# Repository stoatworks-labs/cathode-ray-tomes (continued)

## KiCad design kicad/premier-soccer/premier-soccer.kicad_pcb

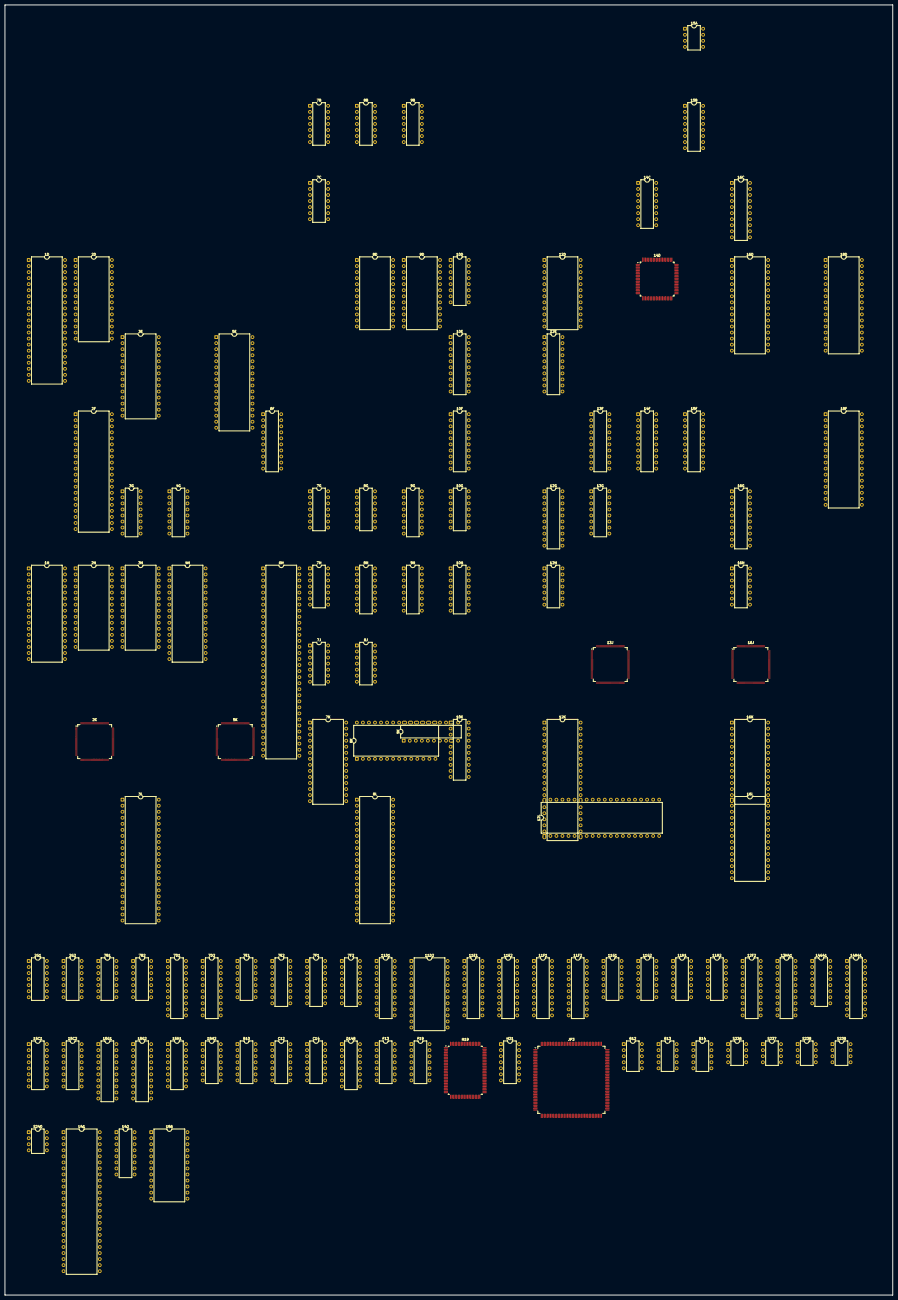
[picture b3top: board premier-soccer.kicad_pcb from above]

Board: 2 copper layers, 373.1 x 542.2 mm, 114 parts (0 on the bottom side), 699 nets, no tracks yet.

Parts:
1D, 3L, 8L: HN624116P; DIP-42_W15.24mm
1H, 4H, 5E: M27C4001; DIP-32_W15.24mm
2D: SRAM32K8B; DIP-28_W15.24mm
2F: Z80CPU; DIP-40_W15.24mm
2G1: 74LS00; DIP-14_W7.62mm
2G2, 7J, 8G: 74LS08; DIP-14_W7.62mm
2H, 3H, 7K, 8K: SRAM64K10; DIP-28_W15.24mm
2K: 053244-A; TQFP-120_14x14mm_P0.4mm
3E: SRAM8K8B; DIP-28_W15.24mm
3G: 74LS139; DIP-16_W7.62mm
4G: 74F138; DIP-16_W7.62mm
5K: 053245-A; TQFP-120_14x14mm_P0.4mm
6F: PAL16L8; DIP-20_W7.62mm
6H: MC68000; DIP-64_W15.24mm
7B, 7B1, 7B2, 8B, 9B: 74LS07; DIP-14_W7.62mm
7C, 7E1, 11H2, 12H, 15H2: 74LS32; DIP-14_W7.62mm
7D1, 7D2, 12G, 16C: 74LS273; DIP-20_W7.62mm
7E2: 74LS138; DIP-16_W7.62mm
7F1, 8H, 9H, 10H, 13G: 74LS157; DIP-16_W7.62mm
7F2, 15C2: 74LS174; DIP-16_W7.62mm
7G, 11H1, 16H: 74LS74; DIP-14_W7.62mm
7H: 74F74; DIP-14_W7.62mm
8D, 9D: HM6116P-3; DIP-24_W15.24mm
8J: 74LS10; DIP-14_W7.62mm
9G: 74LS175; DIP-16_W7.62mm
9K, 10E, 10F, 10K, 11E1, 11F1, 11F2, 12F2, 13H41, 14H41, 16G: 74LS245; DIP-20_W7.62mm
10D, 14G41, 15H1: 74LS367; DIP-16_W7.62mm
10G, 11G1, 11G2: 74LS04; DIP-14_W7.62mm
11D1, 11E2, 12E, 15G1, 15G2: 74LS244; DIP-20_W7.62mm
11D2, 12D: SRAM16KSL45; DIP-24_W15.24mm
12K, 12L: 955D05-06-07-08; DIP-40_W15.24mm
13F, 14F, 15F: 74LS374; DIP-20_W7.62mm
13J: 051962; TQFP-120_14x14mm_P0.4mm
14C, 15B, 15C1: 74LS257; DIP-16_W7.62mm
14D: 053936; PQFP-80_14x14mm_P0.65mm
15A: ER5911; DIP-8_W7.62mm
16D, 18D: 27C1000; DIP-32_W15.24mm
16J: 052109; TQFP-120_14x14mm_P0.4mm
16K, 16L: MB8464A-10W-15W; DIP-28_W15.24mm
18F: DIP-32_W15.24mm
B10: LM324; DIP-14_W7.62mm
C12: 74LS20; DIP-14_W7.62mm
C14: 74LS04; DIP-14_W7.62mm
D14B: 74LS257; DIP-16_W7.62mm
F13: 74LS32; DIP-14_W7.62mm
F19: 74LS74; DIP-14_W7.62mm
H19: 053251; PQFP-100_14x20mm_P0.65mm
H21: 74LS04; DIP-14_W7.62mm
JP3: 054539; PQFP-160_28x28mm_P0.65mm
R12, R13, R14: 052535; DIP-10_W7.62mm
S236, S237, S238, S239, S240: KONAMI_005273; DIP-8_W7.62mm
U41: 054321; DIP-48_W15.24mm
U42: AD1868R; DIP-16_W7.62mm
U56: 051550; DIP-24_W15.24mm

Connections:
/1.54CLK: JP3.28, U41.7, U42.4
/3GA_P5: 2G1.1, 3G.5, U56.1
/3GP4: 3G.4, 7E1.1, 7E1.4, 7G.12
/7E2P13: 7E1.9, 7E1.12, 7E2.13
/11G1P8: 7G.3, 9G.9, 11G1.8, 11H1.11, 16H.11
/11H1P9: 7C.5, 10D.1, 11D1.1, 11D1.19, 11H1.9, 12H.12
/COIN_CNT_1: U56.22, U56.23
/COIN_CNT_2: U56.20, U56.21
/CPU~EN: 5K.26, 11G2.13, 15C1.14, 15H2.5
/DFI0: 13J.59, H19.47
/DFI1: 13J.60, H19.48
/DFI2: 13J.62, H19.49
/DFI3: 13J.63, H19.50
/DFI5: 13J.65, H19.51
/DFI6: 13J.66, H19.52
/DFI7: 13J.67, H19.54
/DO: 15A.4, 15C1.3
/DSA0: 13J.46, H19.57
/DSA1: 13J.47, H19.58
/DSA2: 13J.48, H19.59
/DSA3: 13J.49, H19.60
/DSA5: 13J.51, H19.61
/DSA6: 13J.52, H19.62
/DSA7: 13J.53, H19.63
/DSB0: 13J.30, H19.66
/DSB1: 13J.32, H19.67
/DSB2: 13J.33, H19.68
/DSB3: 13J.34, H19.69
/DSB5: 13J.36, H19.70
/DSB6: 13J.37, H19.71
/DSB7: 13J.38, H19.72
/IOCS: 7E2.15, 14C.15, 15B.15, 15C1.15, D14B.15
/M6: 2K.10, 5K.10, 7D1.11, 7D2.11, 11H1.3, 12G.11, 13F.11, 13J.78, 14D.64, 14F.11, 15F.11, 16H.3, H19.41
/M12: 2K.12, 5K.12, 13J.95
/MAINR~W: 7C.2, 7C.4, 7C.8, 7C.13, U41.31
/MAIN_A1: 1H.12, 2H.10, 3H.10, 4H.12, 6H.29, 7J.5, 8H.2, 11D1.2, 11E2.2, 13J.89, 15G1.2, 15H1.2
/MAIN_A2: 1H.11, 2H.9, 3H.9, 4H.11, 5K.25, 6H.30, 8H.5, 11D1.4, 11E2.4, 15G1.4, 15H1.4
/MAIN_A3: 1H.10, 2H.8, 3H.8, 4H.10, 5K.24, 6H.31, 8H.11, 11D1.6, 11E2.6, 15G1.6, 15H1.6
/MAIN_A4: 1H.9, 2H.7, 3H.7, 4H.9, 5K.23, 6H.32, 8H.14, 11D1.8, 11E2.8, 15G1.8, 15H1.10
/MAIN_A5: 1H.8, 2H.6, 3H.6, 4H.8, 6H.33, 7J.1, 10H.2, 11D1.11, 11E2.11, 15G1.11, 15H1.12
/MAIN_A6: 1H.7, 2H.5, 3H.5, 4H.7, 6H.34, 7J.13, 10H.5, 11D1.13, 11E2.13, 15G1.13, 15H1.14
/MAIN_A7: 1H.6, 2H.4, 3H.4, 4H.6, 5K.22, 6H.35, 10H.11, 11D1.15, 11E2.15, 15G1.15, 16J.114
/MAIN_A8: 1H.5, 2H.3, 3H.3, 4H.5, 5K.20, 6H.36, 10H.14, 11D1.17, 11E2.17, 15G1.17, 16J.113
/MAIN_A9: 1H.27, 2H.25, 3H.25, 4H.27, 5K.19, 6H.37, 9H.2, 10D.2, 12E.2, 15G2.2, 16J.112
/MAIN_A10: 1H.26, 2H.24, 3H.24, 4H.26, 5K.18, 6H.38, 9H.5, 10D.4, 12E.4, 15G2.4, 16J.111
/MAIN_A11: 1H.23, 2H.21, 3H.21, 4H.23, 5K.17, 6H.39, 9H.11, 10D.6, 12E.6, 15G2.6, 16J.110
/MAIN_A12: 1H.25, 2H.23, 3H.23, 4H.25, 5K.15, 6H.40, 7E2.1, 12E.8, 15G2.8
/MAIN_A13: 1H.4, 2H.2, 3H.2, 4H.4, 5K.14, 6H.41, 7E2.2, 12E.11, 15G2.11, 16J.109
/MAIN_A14: 1H.28, 4G.1, 4H.28, 6H.42, 7E2.3, 12E.13, 15G2.13, 16J.80
/MAIN_A15: 1H.29, 4G.2, 4H.29, 6H.43, 12E.15, 15G2.15, 16J.82
/MAIN_A16: 1H.3, 4G.3, 4H.3, 6H.44, 12E.17, 15G2.17, 16J.83
/MAIN_A17: 1H.2, 4G.5, 4H.2, 6H.45, 7E2.6, 10D.12, 14G41.2
/MAIN_A18: 1H.30, 4H.30, 6H.46, 14G41.4
/MAIN_A19: 6H.47, 14G41.6
/MAIN_ABUF0: 2K.19, 15H1.3, 16J.66, H19.85
/MAIN_ABUF1: 2K.18, 15H1.5, 16J.67, H19.84
/MAIN_ABUF2: 2K.17, 15H1.7, 16J.68, H19.83
/MAIN_ABUF3: 2K.15, 15H1.9, 16J.69, H19.82
/MAIN_ABUF4: 15H1.11, 16J.116
/MAIN_ABUF5: 15H1.13, 16J.115
/MAIN_D0: 2K.29, 3H.11, 4H.13, 6H.5, 9K.2, 10F.2, 11F1.2, 14H41.2, 16C.3, 16G.2, D14B.4, H19.80, U41.44
/MAIN_D1: 2K.28, 3H.12, 4H.14, 6H.4, 9K.3, 10F.3, 11F1.3, 14H41.3, 16C.4, 16G.3, D14B.7, H19.79, U41.43
/MAIN_D2: 2K.27, 3H.13, 4H.15, 6H.3, 9K.4, 10F.4, 11F1.4, 14H41.4, 16C.7, 16G.4, D14B.9, H19.77, U41.42
/MAIN_D3: 2K.26, 3H.15, 4H.17, 6H.2, 7E2.14, 9K.5, 10F.5, 11F1.5, 14H41.5, 16C.8, 16G.5, D14B.12, H19.76, U41.41
/MAIN_D4: 2K.25, 3H.16, 4H.18, 6H.1, 9K.6, 10F.6, 11F1.6, 14H41.6, 15B.4, 16C.13, 16G.6, H19.75, U41.40
/MAIN_D5: 2K.24, 3H.17, 4H.19, 6H.64, 9K.7, 10F.7, 11F1.7, 14H41.7, 15B.7, 16C.14, 16G.7, H19.74, U41.39
/MAIN_D6: 2K.23, 3H.18, 4H.20, 6H.63, 9K.8, 10F.8, 11F1.8, 14H41.8, 15B.9, 16C.17, 16G.8, U41.38
/MAIN_D7: 2K.22, 3H.19, 4H.21, 6H.62, 9K.9, 10F.9, 11F1.9, 14H41.9, 15B.12, 16C.18, 16G.9, U41.37
/MAIN_D8: 1H.13, 2H.11, 6H.61, 10K.2, 11F2.2, 12F2.2, 13H41.2, 15C1.4, 15C2.3
/MAIN_D9: 1H.14, 2H.12, 6H.60, 10K.3, 11F2.3, 12F2.3, 13H41.3, 15C1.7, 15C2.4
/MAIN_D10: 1H.15, 2H.13, 6H.59, 10K.4, 11F2.4, 12F2.4, 13H41.4, 15C1.9, 15C2.6
/MAIN_D11: 1H.17, 2H.15, 6H.58, 10K.5, 11F2.5, 12F2.5, 13H41.5, 15C1.12, 15C2.11
/MAIN_D12: 1H.18, 2H.16, 6H.57, 10K.6, 11F2.6, 12F2.6, 13H41.6, 14C.4
/MAIN_D13: 1H.19, 2H.17, 6H.56, 10K.7, 11F2.7, 12F2.7, 13H41.7, 14C.7
/MAIN_D14: 1H.20, 2H.18, 6H.55, 10K.8, 11F2.8, 12F2.8, 13H41.8, 14C.9
/MAIN_D15: 1H.21, 2H.19, 6H.54, 10K.9, 11F2.9, 12F2.9, 13H41.9, 14C.12
/MAIN_DB0: 10E.2, 11E1.2, 13H41.18, 13J.79, 14H41.18, 16J.56
/MAIN_DB1: 10E.3, 11E1.3, 13H41.17, 13J.80, 14H41.17, 16J.57
/MAIN_DB2: 10E.4, 11E1.4, 13H41.16, 13J.81, 14H41.16, 16J.58
/MAIN_DB3: 10E.5, 11E1.5, 13H41.15, 13J.82, 14H41.15, 16J.59
/MAIN_DB4: 10E.6, 11E1.6, 13H41.14, 13J.83, 14H41.14, 16J.60
/MAIN_DB5: 10E.7, 11E1.7, 13H41.13, 13J.84, 14H41.13, 16J.62
/MAIN_DB6: 10E.8, 11E1.8, 13H41.12, 13J.85, 14H41.12, 16J.63
/MAIN_DB7: 10E.9, 11E1.9, 13H41.11, 13J.86, 14H41.11, 16J.64
/MAIN~IRQ: 6H.23, 6H.25, 16J.87
/MBRIT0: 14G41.10, 16C.15
/MBRIT1: 3L.42, 8L.42, 16C.16
/MBRIT2: 11G2.5, 11H2.5, 16C.19
/MCO~WRH: 7C.3, 8D.21
/MCO~WRL: 9D.21, 12H.3
/NDTACK: 11H1.5, 14D.48
/NLOE: 8G.1, 14D.62, 16H.8
/OBJPXL0: 2K.120, H19.30
/OBJPXL1: 2K.119, H19.31
/OBJPXL2: 2K.118, H19.32
/OBJPXL3: 2K.117, H19.33
/OBJPXL4: 2K.116, H19.34
/OBJPXL5: 2K.115, H19.35
/OBJPXL6: 2K.114, H19.36
/OBJPXL7: 2K.113, H19.37
/OBJPXL8: 2K.112, H19.38
/PALETTE~CS: 4G.13, 7C.1, 8H.1, 9H.1, 10E.19, 10H.1, 11E1.19, 12H.1
/PCM0: JP3.34, U41.1
/PCM1: JP3.26, U41.2
/PCM2: JP3.27, U41.3
/PQ: 7G.11, 12H.4, 16J.89
/PR13: 2K.110, H19.25
/PR14: 2K.109, H19.27
/PSACA1: 14C.1, 14D.74, 15B.1, 15C1.1, D14B.1, U41.35
/PSACA2: 14D.72, U41.34
/PSACA3: 14D.71, U41.33
/PSACA4: 14D.70, U41.32
/PSPXL0: 12G.2, H19.4
/PSPXL1: 12G.6, H19.5
/PSPXL2: 12G.12, H19.6
/PSPXL3: 12G.16, H19.7
/PSPXL4: 12G.5, H19.8
/PSPXL5: 12G.9, H19.9
/PSPXL6: 12G.15, H19.10
/RMSCR~RD: 13J.96, 16C.12, 16J.97
/R/~W: 6H.9, 7C.10, 11G1.5, 11H2.2, 12H.9
/SDI0: 2K.108, H19.95
/SDO0: 10G.9, H19.87
/SDON: 7E2.12, U41.30
/SND~CS: 6F.15, U41.20
/SND~IORQ: 2F.20, U41.29
/SND~RD: 2F.21, 3E.22, 6F.2, JP3.67, U41.25
/S~CLK: 2F.6, 7G.5, U41.5
/WD_OUT1: 16C.2, U56.15
/WD_OUT2: 16C.5, U56.16
/ZOE: 10F.19, 11F2.19, 16H.9
/Z_WE1: 7C.6, 11D2.21
/Z_WE2: 12D.21, 12H.11
/colmix/CO1: 8H.3, H19.19
/colmix/CO2: 8H.6, H19.18
/colmix/CO3: 8H.10, H19.17
/colmix/CO4: 8H.13, H19.16
/colmix/CO5: 10H.3, H19.14
/colmix/CO6: 10H.6, H19.13
/colmix/CO7: 10H.10, H19.12
/colmix/CO8: 10H.13, H19.11
/colmix/CO9: 9H.3, H19.93
/colmix/CO10: 9H.6, H19.92
/colmix/CO11: 9H.10, H19.91
/colmix/MCO1: 8D.8, 8H.4, 9D.8
/colmix/MCO2: 8D.7, 8H.7, 9D.7
/colmix/MCO3: 8D.6, 8H.9, 9D.6
/colmix/MCO4: 8D.5, 8H.12, 9D.5
/colmix/MCO5: 8D.4, 9D.4, 10H.4
/colmix/MCO6: 8D.3, 9D.3, 10H.7
/colmix/MCO7: 8D.2, 9D.2, 10H.9
/colmix/MCO8: 8D.1, 9D.1, 10H.12
/colmix/MCO9: 8D.23, 9D.23, 9H.4
/colmix/MCO10: 8D.22, 9D.22, 9H.7
/colmix/MCO11: 8D.19, 9D.19, 9H.9
/colmix/MCO~OE: 8D.20, 9D.20, 9H.12
/colmix/RGB0: 7D1.3, 9D.9, 11E1.18
/colmix/RGB1: 7D1.4, 9D.10, 11E1.17
/colmix/RGB2: 7D1.7, 9D.11, 11E1.16
/colmix/RGB3: 7D1.8, 9D.13, 11E1.15
/colmix/RGB4: 7D1.13, 9D.14, 11E1.14
/colmix/RGB5: 7D1.14, 9D.15, 11E1.13
/colmix/RGB6: 7D1.17, 9D.16, 11E1.12
/colmix/RGB7: 9D.17, 11E1.11
/colmix/RGB8: 7D2.3, 8D.9, 10E.18
/colmix/RGB9: 7D2.4, 8D.10, 10E.17
/colmix/RGB10: 7D2.7, 8D.11, 10E.16
/colmix/RGB11: 7D2.8, 8D.13, 10E.15
/colmix/RGB12: 7D2.13, 8D.14, 10E.14
/colmix/RGB13: 7D2.14, 8D.15, 10E.13
/colmix/RGB14: 7D2.17, 8D.16, 10E.12
/colmix/RGB15: 7D2.18, 8D.17, 10E.11
/colmix/rgb/B0: 7B1.5, 7D1.16
/colmix/rgb/B1: 7B1.9, 7D1.15
/colmix/rgb/B2: 7B1.3, 7D1.12
/colmix/rgb/B3: 7D1.9, 9B.9
/colmix/rgb/B4: 7B1.1, 7D1.6
/colmix/rgb/G0: 7D1.5, 9B.5
/colmix/rgb/G1: 7D1.2, 8B.13
/colmix/rgb/G2: 7D2.19, 9B.3
/colmix/rgb/G3: 7D2.16, 8B.11
/colmix/rgb/G4: 7D2.15, 9B.1
/colmix/rgb/R0: 7D2.12, 8B.5
/colmix/rgb/R1: 7D2.9, 8B.9
/colmix/rgb/R2: 7D2.6, 9B.13
/colmix/rgb/R3: 7D2.5, 8B.3
/colmix/rgb/R4: 7D2.2, 9B.11
/colmix/rgb/~SHADOW: 7B.3, 7B.5, 7B.13, 7D1.19
/io_cabinet/I1P_BTN_1: 15B.2, S237.1
/io_cabinet/I1P_BTN_2: 15B.5, S237.3
/io_cabinet/I1P_BTN_3: 15B.11, S237.5
/io_cabinet/I1P_DOWN: D14B.14, S236.7
/io_cabinet/I1P_LEFT: D14B.2, S236.1
/io_cabinet/I1P_RIGHT: D14B.5, S236.3
/io_cabinet/I1P_START: 15B.14, S240.1
/io_cabinet/I1P_UP: D14B.11, S236.5
/io_cabinet/I2P_BTN_1: 15B.3, S239.1
/io_cabinet/I2P_BTN_2: 15B.6, S239.3
/io_cabinet/I2P_BTN_3: 15B.10, S239.5
/io_cabinet/I2P_DOWN: D14B.13, S238.7
/io_cabinet/I2P_LEFT: D14B.3, S238.1
/io_cabinet/I2P_RIGHT: D14B.6, S238.3
/io_cabinet/I2P_START: 15B.13, S240.3
/io_cabinet/I2P_UP: D14B.10, S238.5
/io_cabinet/ICOIN_1: 15C1.11, S237.7
/io_cabinet/ICOIN_2: 15C1.10, S239.7
/io_cabinet/ISERVICE1: 15C1.2, S240.5
/main/3G P11: 3G.11, 4G.4, 7E2.4
/main/4GP12: 4G.12, 8G.9, 11H1.12
/main/7CP11: 3H.27, 7C.11
/main/7HP6: 7H.2, 7H.6, 11G1.9
/main/9GP11: 8J.1, 9G.11
/main/10GP6: 4G.6, 8J.5, 8J.9, 9G.4, 10G.6, 11H1.10, 16H.10
/main/11H2 P11: 3G.15, 11H2.11
/main/MAIN_A20: 3G.14, 6H.48
/main/MAIN_A21: 3G.2, 3G.13, 6H.50, 8J.13
/main/MAIN_A23: 6H.52, 8J.3, 10G.11, 11H2.12
/main/MAIN~CLK: 6H.15, 7H.5
/main/VSS: 1H.1, 3G.3, 4H.1, 9G.13, 16H.2
/main/~AS: 6H.6, 7E2.5, 10G.5, 11H2.13
/main/~DTACK: 6H.10, 8J.8
/main/~HALT: 6H.17, 7B2.10
/main/~RAM_CS: 4G.15, 7C.12, 15H2.10, 15H2.12
/main/~ROM_CS: 1H.24, 3G.12, 4H.24
/main/~VPA: 6H.21, 8J.6
/objects/AR0: 2K.30, 5K.119
/objects/AR1: 2K.32, 5K.118
/objects/AR2: 2K.33, 5K.117
/objects/AROK: 2K.34, 5K.116
/objects/BR0: 2K.35, 5K.115
/objects/BR1: 2K.36, 5K.114
/objects/BR2: 2K.37, 5K.113
/objects/BROK: 2K.38, 5K.112
/objects/CLAT: 2K.64, 5K.86
/objects/CPUA1: 7J.6, 7K.10, 8K.10
/objects/CPUA5: 7J.3, 7K.6, 8K.6
/objects/CPUA6: 7J.11, 7K.5, 8K.5
/objects/HP0: 2K.54, 5K.96
/objects/HP1: 2K.53, 5K.97
/objects/HP2: 2K.52, 5K.98
/objects/HP3: 2K.50, 5K.99
/objects/HP4: 2K.49, 5K.100
/objects/HP5: 2K.48, 5K.102
/objects/HP6: 2K.47, 5K.103
/objects/HP7: 2K.45, 5K.104
/objects/HP8: 2K.44, 5K.105
/objects/HP9: 2K.43, 5K.107
/objects/HRFP: 2K.39, 5K.110
/objects/OBJRAMD0: 5K.45, 7K.11, 9K.18
/objects/OBJRAMD1: 5K.44, 7K.12, 9K.17
/objects/OBJRAMD2: 5K.43, 7K.13, 9K.16
/objects/OBJRAMD3: 5K.42, 7K.15, 9K.15
/objects/OBJRAMD4: 5K.40, 7K.16, 9K.14
/objects/OBJRAMD5: 5K.39, 7K.17, 9K.13
/objects/OBJRAMD6: 5K.38, 7K.18, 9K.12
/objects/OBJRAMD7: 5K.37, 7K.19, 9K.11
/objects/OBJRAMD8: 5K.35, 8K.11, 10K.18
/objects/OBJRAMD9: 5K.34, 8K.12, 10K.17
/objects/OBJRAMD10: 5K.33, 8K.13, 10K.16
/objects/OBJRAMD11: 5K.32, 8K.15, 10K.15
/objects/OBJRAMD12: 5K.30, 8K.16, 10K.14
/objects/OBJRAMD13: 5K.29, 8K.17, 10K.13
/objects/OBJRAMD14: 5K.28, 8K.18, 10K.12
/objects/OBJRAMD15: 5K.27, 8K.19, 10K.11
/objects/OBJROMA0: 3L.10, 5K.85, 8L.10
/objects/OBJROMA1: 3L.9, 5K.84, 8L.9
/objects/OBJROMA2: 3L.8, 5K.83, 8L.8
/objects/OBJROMA3: 3L.7, 5K.82, 8L.7
/objects/OBJROMA4: 3L.6, 5K.80, 8L.6
/objects/OBJROMA5: 3L.5, 5K.79, 8L.5
/objects/OBJROMA6: 3L.4, 5K.78, 8L.4
/objects/OBJROMA7: 3L.3, 5K.77, 8L.3
/objects/OBJROMA8: 3L.41, 5K.75, 8L.41
/objects/OBJROMA9: 3L.40, 5K.74, 8L.40
/objects/OBJROMA10: 3L.39, 5K.73, 8L.39
/objects/OBJROMA11: 3L.38, 5K.72, 8L.38
/objects/OBJROMA12: 3L.37, 5K.70, 8L.37
/objects/OBJROMA13: 3L.36, 5K.69, 8L.36
/objects/OBJROMA14: 3L.35, 5K.68, 8L.35
/objects/OBJROMA15: 3L.34, 5K.67, 8L.34
/objects/OBJROMA16: 3L.33, 5K.66, 8L.33
/objects/OBJROMA17: 3L.2, 5K.65, 8L.2
/objects/OBJROMA18: 3L.1, 5K.64, 8L.1
/objects/OBJROMD0: 2K.100, 3L.14
/objects/OBJROMD1: 2K.99, 3L.16
/objects/OBJROMD2: 2K.98, 3L.18
/objects/OBJROMD3: 2K.97, 3L.20
/objects/OBJROMD4: 2K.96, 3L.23
/objects/OBJROMD5: 2K.95, 3L.25
/objects/OBJROMD6: 2K.94, 3L.27
/objects/OBJROMD7: 2K.93, 3L.29
/objects/OBJROMD8: 2K.92, 8L.14
/objects/OBJROMD9: 2K.90, 8L.16
/objects/OBJROMD10: 2K.89, 8L.18
/objects/OBJROMD11: 2K.88, 8L.20
/objects/OBJROMD12: 2K.87, 8L.23
/objects/OBJROMD13: 2K.86, 8L.25
/objects/OBJROMD14: 2K.85, 8L.27
/objects/OBJROMD15: 2K.84, 8L.29
/objects/OBJROMD16: 2K.83, 3L.15
/objects/OBJROMD17: 2K.82, 3L.17
/objects/OBJROMD18: 2K.80, 3L.19
/objects/OBJROMD19: 2K.79, 3L.21
/objects/OBJROMD20: 2K.78, 3L.24
/objects/OBJROMD21: 2K.77, 3L.26
/objects/OBJROMD22: 2K.75, 3L.28
/objects/OBJROMD23: 2K.74, 3L.30
/objects/OBJROMD24: 2K.73, 8L.15
/objects/OBJROMD25: 2K.72, 8L.17
/objects/OBJROMD26: 2K.70, 8L.19
/objects/OBJROMD27: 2K.69, 8L.21
/objects/OBJROMD28: 2K.68, 8L.24
/objects/OBJROMD29: 2K.67, 8L.26
/objects/OBJROMD30: 2K.66, 8L.28
/objects/OBJROMD31: 2K.65, 8L.30
/objects/ORAMA1: 5K.52, 7K.9, 8K.9
/objects/ORAMA2: 5K.53, 7K.8, 8K.8
/objects/ORAMA3: 5K.54, 7K.7, 8K.7
/objects/ORAMA4: 5K.55, 7K.4, 8K.4
/objects/ORAMA5: 5K.56, 7K.3, 8K.3
/objects/ORAMA6: 5K.57, 7K.25, 8K.25
/objects/ORAMA7: 5K.58, 7K.24, 8K.24
/objects/ORAMA8: 5K.59, 7K.21, 8K.21
/objects/ORAMA9: 5K.62, 7K.23, 8K.23
/objects/ORAMA10: 5K.63, 7K.2, 8K.2
/objects/PL0: 2K.63, 5K.87
/objects/PL1: 2K.62, 5K.88
/objects/PL2: 2K.60, 5K.89
/objects/PL3: 2K.59, 5K.90
/objects/PL4: 2K.58, 5K.92
/objects/PL5: 2K.57, 5K.93
/objects/PL6: 2K.56, 5K.94
/objects/R~OE: 5K.49, 7K.22, 8K.22
/objects/SHADOW: 2K.55, 5K.95
/objects/~HIT: 2K.42, 5K.108
/objects/~OBJRAM_RD: 9K.1, 10K.1, 11H2.8
/objects/~WE1: 5K.48, 7K.27
/objects/~WE2: 5K.47, 8K.27
/objects/~ZLD: 2K.40, 5K.109
/psac/11H2P6: 10D.15, 10G.1, 11E2.1, 11E2.19, 11F1.19, 11H2.6, 12E.1, 12E.19, 12F2.19
/psac/DZ0: 10F.18, 11D2.9, 14D.29
/psac/DZ1: 10F.17, 11D2.10, 14D.30
/psac/DZ2: 10F.16, 11D2.11, 14D.31
/psac/DZ3: 10F.15, 11D2.13, 14D.32
/psac/DZ4: 10F.14, 11D2.14, 14D.34
/psac/DZ5: 10F.13, 11D2.15, 14D.35
/psac/DZ6: 10F.12, 11D2.16, 14D.36
/psac/DZ7: 10F.11, 11D2.17, 14D.37
/psac/DZ8: 11F2.18, 12D.9, 14D.38
/psac/DZ9: 11F2.17, 12D.10, 14D.39
/psac/DZ10: 11F2.16, 12D.11, 14D.40
/psac/DZ11: 11F2.15, 12D.13, 14D.41
/psac/DZ12: 11F2.14, 12D.14, 14D.43
/psac/DZ13: 11F2.13, 12D.15, 14D.44
/psac/DZ14: 11F2.12, 12D.16, 14D.45
/psac/DZ15: 11F2.11, 12D.17, 14D.46
/psac/LA0: 11D1.14, 11D2.6, 12D.6, 14D.53
/psac/LA1: 11D1.12, 11D2.5, 12D.5, 14D.54
/psac/LA2: 11D1.9, 11D2.4, 12D.4, 14D.55
/psac/LA3: 11D1.7, 11D2.3, 12D.3, 14D.56
/psac/LA4: 11D1.5, 11D2.2, 12D.2, 14D.57
/psac/LA5: 11D1.3, 11D2.1, 12D.1, 14D.58
/psac/LA6: 10D.3, 11D2.23, 12D.23, 14D.59
/psac/LA7: 10D.5, 11D2.22, 12D.22, 14D.60
/psac/LA8: 10D.7, 11D2.19, 12D.19, 14D.61
/psac/LH1: 11D1.18, 11D2.8, 12D.8, 14D.50
/psac/LH2: 11D1.16, 11D2.7, 12D.7, 14D.51
/psac/NOB: 10G.3, 14D.76
/psac/NOE: 10G.2, 14D.28
/psac/PREPXL4: 12G.4, 14F.15
/psac/PREPXL5: 12G.8, 14F.16
/psac/PREPXL6: 12G.14, 14F.19
/psac/PSD0: 13G.2, 16G.18, 18F.13
/psac/PSD1: 13G.5, 16G.17, 18F.14
/psac/PSD2: 13G.11, 16G.16, 18F.15
/psac/PSD3: 13G.14, 16G.15, 18F.17
/psac/PSD4: 13G.3, 16G.14, 18F.18
/psac/PSD5: 13G.6, 16G.13, 18F.19
/psac/PSD6: 13G.10, 16G.12, 18F.20
/psac/PSD7: 13G.13, 16G.11, 18F.21
/psac/SEL: 13G.1, 15F.2
/psac/X0: 14D.26, 15F.3
/psac/X1: 14D.25, 15F.4
/psac/X2: 14D.24, 15F.7
/psac/X3: 14D.22, 15F.8
/psac/X4: 11E2.18, 14D.21, 16D.12, 18D.12
/psac/X5: 11E2.16, 14D.20, 16D.11, 18D.11
/psac/X6: 11E2.14, 14D.19, 16D.10, 18D.10
/psac/X7: 11E2.12, 14D.18, 16D.9, 18D.9
/psac/X8: 11E2.9, 14D.17, 16D.8, 18D.8
/psac/X9: 11E2.7, 14D.16, 16D.7, 18D.7
/psac/X10: 11E2.5, 14D.15, 16D.6, 18D.6
/psac/X11: 11E2.3, 14D.14, 16D.5, 18D.5
/psac/X12: 12E.18, 14D.13, 16D.27, 18D.27
/psac/Y0: 14D.10, 15F.13
/psac/Y1: 14D.9, 15F.14
/psac/Y2: 14D.8, 15F.17
/psac/Y3: 14D.7, 15F.18
/psac/Y4: 12E.16, 14D.6, 16D.26, 18D.26
/psac/Y5: 12E.14, 14D.5, 16D.23, 18D.23
/psac/Y6: 12E.12, 14D.4, 16D.25, 18D.25
/psac/Y7: 12E.9, 14D.3, 16D.4, 18D.4
/psac/Y8: 12E.7, 14D.1, 16D.28, 18D.28
/psac/Y9: 12E.5, 14D.80, 16D.29, 18D.29
/psac/Y10: 12E.3, 14D.79, 16D.3, 18D.3
/psac/Y11: 10D.11, 14D.78, 16D.2, 18D.2
/psac/ZA0: 15F.5, 15G1.18, 18F.12
/psac/ZA1: 15F.6, 15G1.16, 18F.11
/psac/ZA2: 15F.9, 15G1.14, 18F.10
/psac/ZA3: 15F.12, 15G1.12, 18F.9
/psac/ZA4: 15F.15, 15G1.9, 18F.8
/psac/ZA5: 15F.16, 15G1.7, 18F.7
/psac/ZA6: 15F.19, 15G1.5, 18F.6
/psac/ZA7: 13F.2, 15G1.3, 18F.5
/psac/ZA8: 13F.5, 15G2.18, 18F.27
/psac/ZA9: 13F.6, 15G2.16, 18F.26
/psac/ZA10: 13F.12, 15G2.12, 18F.25
/psac/ZA11: 13F.9, 18F.23
/psac/ZA12: 13F.15, 15G2.9, 18F.4
/psac/ZA13: 13F.16, 15G2.7, 18F.28
/psac/ZA14: 13F.19, 15G2.5, 18F.29
/psac/ZA15: 14F.2, 15G2.3, 18F.3
/psac/ZA16: 14F.5, 14G41.3, 18F.2
/psac/ZA17: 14F.6, 14G41.5, 18F.30
/psac/ZA18: 14F.9, 14G41.7, 18F.31
/psac/ZROMD0: 11F1.18, 13F.3, 16D.13
/psac/ZROMD1: 11F1.17, 13F.4, 16D.14
/psac/ZROMD2: 11F1.16, 13F.7, 16D.15
/psac/ZROMD3: 11F1.15, 13F.8, 16D.17
/psac/ZROMD4: 11F1.14, 13F.13, 16D.18
/psac/ZROMD5: 11F1.13, 13F.14, 16D.19
/psac/ZROMD6: 11F1.12, 13F.17, 16D.20
/psac/ZROMD7: 11F1.11, 13F.18, 16D.21
/psac/ZROMD8: 12F2.18, 14F.3, 18D.13
/psac/ZROMD9: 12F2.17, 14F.4, 18D.14
/psac/ZROMD10: 12F2.16, 14F.7, 18D.15
/psac/ZROMD11: 12F2.15, 14F.8, 18D.17
/psac/ZROMD12: 12F2.14, 14F.13, 18D.18
/psac/ZROMD13: 12F2.13, 14F.14, 18D.19
/psac/ZROMD14: 12F2.12, 14F.17, 18D.20
/psac/ZROMD15: 12F2.11, 14F.18, 18D.21
/psac/Z~OE: 14F.12, 15G2.14, 18F.24
/psac/~CPU: 11G2.3, 14G41.1, 14G41.15, 15G1.1, 15G1.19, 15G2.1, 15G2.19, 15H2.3, 16G.19
/scroll/COL5: 13J.109, 16J.42
/scroll/COL6: 13J.108, 16J.43
/scroll/COL7: 13J.107, 16J.46
/scroll/GFXROMA0: 12K.9, 12L.9, 16J.35
/scroll/GFXROMA1: 12K.8, 12L.8, 16J.34
/scroll/GFXROMA2: 12K.7, 12L.7, 16J.33
/scroll/GFXROMA3: 12K.6, 12L.6, 16J.32
/scroll/GFXROMA4: 12K.5, 12L.5, 16J.30
/scroll/GFXROMA5: 12K.4, 12L.4, 16J.29
/scroll/GFXROMA6: 12K.3, 12L.3, 16J.28
/scroll/GFXROMA7: 12K.2, 12L.2, 16J.27
/scroll/GFXROMA8: 12K.40, 12L.40, 16J.26
/scroll/GFXROMA9: 12K.39, 12L.39, 16J.25
/scroll/GFXROMA10: 12K.38, 12L.38, 16J.24
/scroll/GFXROMA11: 12K.37, 12L.37, 16J.37
/scroll/GFXROMA12: 12K.36, 12L.36, 16J.38
/scroll/GFXROMA13: 12K.35, 12L.35, 16J.41
/scroll/GFXROMA14: 12K.34, 12L.34, 16J.39
/scroll/GFXROMA15: 12K.33, 12L.33, 16J.40
/scroll/GFXROMA16: 12K.32, 12L.32, 16J.23
/scroll/GFXROMA17: 12K.1, 12L.1, 16J.22
/scroll/GFXROMD0: 12L.13, 13J.29
/scroll/GFXROMD1: 12L.15, 13J.28
/scroll/GFXROMD2: 12L.17, 13J.27
/scroll/GFXROMD3: 12L.19, 13J.26
/scroll/GFXROMD4: 12L.22, 13J.25
/scroll/GFXROMD5: 12L.24, 13J.24
/scroll/GFXROMD6: 12L.26, 13J.23
/scroll/GFXROMD7: 12L.28, 13J.22
/scroll/GFXROMD8: 12K.13, 13J.21
/scroll/GFXROMD9: 12K.15, 13J.20
/scroll/GFXROMD10: 12K.17, 13J.19
/scroll/GFXROMD11: 12K.19, 13J.18
/scroll/GFXROMD12: 12K.22, 13J.17
/scroll/GFXROMD13: 12K.24, 13J.16
/scroll/GFXROMD14: 12K.26, 13J.13
/scroll/GFXROMD15: 12K.28, 13J.12
/scroll/GFXROMD16: 12L.14, 13J.11
/scroll/GFXROMD17: 12L.16, 13J.10
/scroll/GFXROMD18: 12L.18, 13J.9
/scroll/GFXROMD19: 12L.20, 13J.8
/scroll/GFXROMD20: 12L.23, 13J.7
/scroll/GFXROMD21: 12L.25, 13J.6
/scroll/GFXROMD22: 12L.27, 13J.5
/scroll/GFXROMD23: 12L.29, 13J.4
/scroll/GFXROMD24: 12K.14, 13J.3
/scroll/GFXROMD25: 12K.16, 13J.2
/scroll/GFXROMD26: 12K.18, 13J.120
/scroll/GFXROMD27: 12K.20, 13J.119
/scroll/GFXROMD28: 12K.23, 13J.118
/scroll/GFXROMD29: 12K.25, 13J.117
/scroll/GFXROMD30: 12K.27, 13J.116
/scroll/GFXROMD31: 12K.29, 13J.115
/scroll/M24: 7H.11, 11G1.2, 13J.90, 16J.65
/scroll/SCRAMA0: 16J.2, 16K.10, 16L.10
/scroll/SCRAMA1: 16J.120, 16K.9, 16L.9
/scroll/SCRAMA2: 16J.119, 16K.8, 16L.8
/scroll/SCRAMA3: 16J.118, 16K.7, 16L.7
/scroll/SCRAMA4: 16J.117, 16K.6, 16L.6
/scroll/SCRAMA5: 16J.70, 16K.5, 16L.5
/scroll/SCRAMA6: 16J.71, 16K.4, 16L.4
/scroll/SCRAMA7: 16J.72, 16K.3, 16L.3
/scroll/SCRAMA8: 16J.73, 16K.25, 16L.25
/scroll/SCRAMA9: 16J.76, 16K.24, 16L.24
/scroll/SCRAMA10: 16J.77, 16K.21, 16L.21
/scroll/SCRAMA11: 16J.78, 16K.23, 16L.23
/scroll/SCRAMA12: 16J.79, 16K.2, 16L.2
/scroll/VD0: 16J.20, 16K.11
/scroll/VD1: 16J.19, 16K.12
/scroll/VD2: 16J.18, 16K.13
/scroll/VD3: 16J.17, 16K.15
/scroll/VD4: 16J.16, 16K.16
/scroll/VD5: 16J.13, 16K.17
/scroll/VD6: 16J.12, 16K.18
/scroll/VD7: 16J.11, 16K.19
/scroll/VD8: 16J.10, 16L.11
/scroll/VD9: 16J.9, 16L.12
/scroll/VD10: 16J.8, 16L.13
/scroll/VD11: 16J.7, 16L.15
/scroll/VD12: 16J.6, 16L.16
/scroll/VD13: 16J.5, 16L.17
/scroll/VD14: 16J.4, 16L.18
/scroll/VD15: 16J.3, 16L.19
/scroll/ZA1H: 13J.101, 16J.50
/scroll/ZA2H: 13J.100, 16J.51
/scroll/ZA4H: 13J.99, 16J.52
/scroll/ZB1H: 13J.106, 16J.47
/scroll/ZB2H: 13J.103, 16J.48
/scroll/ZB4H: 13J.102, 16J.49
/scroll/~BE: 13J.98, 16J.53
/scroll/~RCS1: 16J.93, 16L.20
/scroll/~ROE1: 16J.95, 16L.22
/scroll/~ROE2: 16J.96, 16K.22
/scroll/~RWE1: 16J.107, 16L.27
/scroll/~RWE2: 16J.108, 16K.27
/sound/054986A/DL: U41.9, U42.3
/sound/054986A/DR: U41.11, U42.5
/sound/054986A/GND: U41.6, U41.27, U41.28
/sound/054986A/LL: U41.10, U42.2, U42.6
/sound/054986A/VSS: U42.7, U42.12
/sound/BANK0: 7F1.3, 7F2.2
/sound/BANK1: 7F1.6, 7F2.5
/sound/BANK2: 7F1.10, 7F2.7
/sound/BANK3: 7F1.13, 7F2.10
/sound/BUSY: 2G2.1, JP3.11
/sound/R~W: 2D.27, JP3.107
/sound/SNDR_A0: 1D.30, 2D.10, JP3.132
/sound/SNDR_A1: 1D.10, 2D.9, JP3.135
/sound/SNDR_A2: 1D.9, 2D.8, JP3.137
/sound/SNDR_A3: 1D.8, 2D.7, JP3.141
/sound/SNDR_A4: 1D.7, 2D.6, JP3.143
/sound/SNDR_A5: 1D.6, 2D.5, JP3.146
/sound/SNDR_A6: 1D.5, 2D.4, JP3.148
/sound/SNDR_A7: 1D.4, 2D.3, JP3.151
/sound/SNDR_A8: 1D.3, 2D.25, JP3.153
/sound/SNDR_A9: 1D.41, 2D.24, JP3.157
/sound/SNDR_A10: 1D.40, 2D.21, JP3.154
/sound/SNDR_A11: 1D.39, 2D.23, JP3.152
/sound/SNDR_A12: 1D.38, 2D.2, JP3.149
/sound/SNDR_A13: 1D.37, 2D.26, JP3.147
/sound/SNDR_A14: 1D.36, JP3.144
/sound/SNDR_A15: 1D.35, JP3.142
/sound/SNDR_A16: 1D.34, 2D.1, JP3.138
/sound/SNDR_A17: 1D.33, JP3.136
/sound/SNDR_A18: 1D.2, JP3.156
/sound/SNDR_A19: 1D.1, JP3.158
/sound/SNDR_A20: 1D.42, JP3.159
/sound/SNDR_D0: 1D.14, 2D.11, JP3.128
/sound/SNDR_D1: 1D.16, 2D.12, JP3.126
/sound/SNDR_D2: 1D.18, 2D.13, JP3.124
/sound/SNDR_D3: 1D.20, 2D.15, JP3.122
/sound/SNDR_D4: 1D.23, 2D.16, JP3.123
/sound/SNDR_D5: 1D.25, 2D.17, JP3.125
/sound/SNDR_D6: 1D.27, 2D.18, JP3.127
/sound/SNDR_D7: 1D.29, 2D.19, JP3.129
/sound/SND_A0: 2F.30, 3E.10, 5E.12, JP3.52
/sound/SND_A1: 2F.31, 3E.9, 5E.11, JP3.51
/sound/SND_A2: 2F.32, 3E.8, 5E.10, JP3.49
/sound/SND_A3: 2F.33, 3E.7, 5E.9, JP3.48
/sound/SND_A4: 2F.34, 3E.6, 5E.8, JP3.47
/sound/SND_A5: 2F.35, 3E.5, 5E.7, JP3.46
/sound/SND_A6: 2F.36, 3E.4, 5E.6, JP3.45
/sound/SND_A7: 2F.37, 3E.3, 5E.5, JP3.44
/sound/SND_A8: 2F.38, 3E.25, 5E.27, JP3.42
/sound/SND_A9: 2F.39, 3E.24, 5E.26
/sound/SND_A10: 2F.40, 3E.21, 5E.23, 6F.8
/sound/SND_A11: 2F.1, 3E.23, 5E.25, 6F.9
/sound/SND_A12: 2F.2, 3E.2, 5E.4
/sound/SND_A13: 2F.3, 5E.28, 6F.7
/sound/SND_A14: 2F.4, 6F.6, 7F1.2
/sound/SND_A15: 2F.5, 6F.5, 7F1.1
/sound/SND_D0: 2F.14, 3E.11, 5E.13, 7F2.3, JP3.9
/sound/SND_D1: 2F.15, 3E.12, 5E.14, 7F2.4, JP3.8
/sound/SND_D2: 2F.12, 3E.13, 5E.15, 7F2.6, JP3.7
/sound/SND_D3: 2F.8, 3E.15, 5E.17, 7F2.11, JP3.6
/sound/SND_D4: 2F.7, 3E.16, 5E.18, JP3.5
/sound/SND_D5: 2F.9, 3E.17, 5E.19, JP3.4
/sound/SND_D6: 2F.10, 3E.18, 5E.20, JP3.3
/sound/SND_D7: 2F.13, 3E.19, 5E.21, JP3.2
/sound/S~CS: 6F.17, JP3.69
/sound/S~MREQ: 2F.19, 6F.4
/sound/S~WR: 2F.22, 3E.27, 6F.1, JP3.68
/sound/~BUSACK: 2F.23, 6F.11
/sound/~CE: 1D.11, JP3.133
/sound/~CS1: 3E.20, 6F.18
/sound/~CS: 2D.20, JP3.109
/sound/~NMI: 2F.17, JP3.12
/sound/~OE1: 2D.22, JP3.108
/sound/~OE2: 1D.13, JP3.131
/sound/~RFSH: 2F.28, 6F.3
/sound/~ROM_CS: 5E.24, 6F.19
/~HBLANK: 7J.9, 13J.70
/~HSYNC: 2K.8, 5K.4, 13J.73, 14D.65
/~INT: 2F.16, U41.8
/~LDS: 2G1.5, 2K.14, 5K.9, 6H.8, 7C.9, 7E1.2, 7E1.10, 13J.88, 14D.68
/~MRESET: 6H.18, 7B2.8, U41.4
/~NWCS: 4G.9, 8G.10, 14D.69
/~OBJSET0: 4G.11, 5K.6, 8G.4, 11G2.11
/~OBJSET1: 2K.13, 4G.10
/~OBJ_CS: 4G.14, 8G.5, 12H.10
/~PCU_CS: 4G.7, H19.81
/~PSAC: 2G1.2, 3G.9, 11H2.4, 15H2.2
/~RCS0: 2K.3, 5K.3, 16J.92
/~RD: 2K.20, 5K.13, 8G.2, 9H.14, 10E.1, 10F.1, 11E1.1, 11F1.1, 11F2.1, 11G1.6, 11H2.10, 12F2.1, 13H41.1, 13J.87, 14H41.1, 15H2.9, 16G.1, 16J.85
/~RESET: 2F.26, 7F2.1, 7H.9, 13J.92, 15C2.1, 16C.1, 16J.55, JP3.71
/~RST: 7B2.9, 7B2.11, 16J.98
/~UDS: 2G1.4, 5K.8, 6H.7, 7E1.5, 7E1.13, 11H2.1, 16J.81
/~VBLANK: 7J.10, 13J.69
/~VCS: 7G.9, 12H.5, 13J.97, 16J.54, 16J.84
/~VSYNC: 2K.9, 5K.5, 13J.72, 14D.66
/~WAIT: 2G2.2, U41.23
/~WDRST: 7H.12, 7H.13, U56.10
GND: 1D.12, 1D.31, 1D.32, 1H.16, 1H.22, 2D.14, 2F.29, 2G1.7, 2G2.7, 2H.14, 2H.20, 2K.1, 2K.2, 2K.11, 2K.21, 2K.31, 2K.41, 2K.51, 2K.61, 2K.71, 2K.81, 2K.91, 2K.101, 2K.111, 3E.14, 3G.8, 3H.14, 3H.20, 3L.11, 3L.12, 3L.13, 3L.31, 4G.8, 4H.16, 4H.22, 5E.16, 5E.22, 5K.1, 5K.2, 5K.11, 5K.21, 5K.31, 5K.41, 5K.51, 5K.61, 5K.71, 5K.81, 5K.91, 5K.101, 5K.111, 6F.10, 6H.16, 6H.53, 7B.7, 7B1.7, 7B2.7, 7C.7, 7E1.7, 7E2.8, 7F1.5, 7F1.11, 7F1.14, 7F1.15, 7F2.8, 7F2.13, 7F2.14, 7G.7, 7H.7, 7J.7, 7K.14, 7K.26, 8B.7, 8D.12, 8D.18, 8G.7, 8H.15, 8J.7, 8K.14, 8K.26, 8L.11, 8L.12, 8L.13, 8L.31, 9B.7, 9D.12, 9D.18, 9G.8, 9H.13, 9H.15, 10D.8, 10D.10, 10D.14, 10G.7, 10H.15, 11D1.10, 11D2.12, 11D2.18, 11E2.10, 11G1.7, 11G2.7, 11H1.7, 11H2.7, 12D.12, 12D.18, 12E.10, 12G.10, 12H.7, 12K.10, 12K.11, 12K.12, 12K.30, 12L.10, 12L.11, 12L.12, 12L.30, 13J.1, 13J.15, 13J.31, 13J.45, 13J.61, 13J.75, 13J.91, 13J.94, 13J.105, 13J.110, 13J.111, 13J.112, 13J.113, 14D.2, 14D.12, 14D.23, 14D.42, 14D.52, 14D.63, 14D.75, 14G41.8, 14G41.12, 14G41.14, 15A.5, 15A.6, 15C1.6, 15C2.8, 15C2.13, 15C2.14, 15G1.10, 15G2.10, 15H1.1, 15H1.8, 15H1.15, 15H2.7, 16D.16, 16D.22, 16D.24, 16H.7, 16J.1, 16J.15, 16J.21, 16J.31, 16J.45, 16J.61, 16J.75, 16J.91, 16J.105, 16K.14, 16K.20, 16L.14, 18D.16, 18D.22, 18D.24, 18F.16, 18F.22, B10.11, C12.7, C14.7, F13.7, F19.7, H19.15, H19.20, H19.21, H19.22, H19.23, H19.24, H19.40, H19.55, H19.56, H19.65, H19.73, H19.90, H19.94, H19.96, H21.7, JP3.1, JP3.10, JP3.30, JP3.36, JP3.37, JP3.38, JP3.39, JP3.41, JP3.50, JP3.56, JP3.57, JP3.59, JP3.61, JP3.62, JP3.65, JP3.66, JP3.70, JP3.72, JP3.73, JP3.74, JP3.81, JP3.90, JP3.110, JP3.121, JP3.130, JP3.139, JP3.150, R12.9, R13.9, R14.9, U56.13, U56.14
unnamed: 2F.24, 2G2.3
unnamed: 2H.22, 3H.22, 15H2.8
unnamed: 2H.27, 15H2.11
unnamed: 3G.1, 3G.10
unnamed: 5E.29, 7F1.4
unnamed: 5E.3, 7F1.7
unnamed: 5E.2, 7F1.9
unnamed: 5K.7, 12H.8
unnamed: 6F.14, 7F2.9
unnamed: 7B1.11, 7B1.13, 7J.8, 8B.1
unnamed: 7D1.18, 10G.8
unnamed: 7G.2, 7G.6
unnamed: 2G1.6, 7G.10
unnamed: 8J.11, 8J.12
unnamed: 9G.2, 9G.5
unnamed: 9G.7, 9G.12
unnamed: 2G1.3, 9G.1
unnamed: 8J.10, 10G.10
unnamed: 9K.19, 10K.19, 15H2.6
unnamed: 8G.3, 11D2.20, 12D.20
unnamed: 11G2.6, 15H2.1
unnamed: 11G2.10, 11H2.9
unnamed: 7J.2, 7J.4, 7J.12, 11G2.12
unnamed: 11H1.2, 16H.5
unnamed: 8G.8, 11H1.4, 16H.4, 16H.12
unnamed: 11H2.3, 12H.2, 12H.13
unnamed: 12G.3, 13G.4
unnamed: 12G.7, 13G.7
unnamed: 12G.13, 13G.9
unnamed: 12G.17, 13G.12
unnamed: 10G.4, 12G.18
unnamed: 12G.19, 13G.15
unnamed: 8J.2, 12H.6
unnamed: 11G2.4, 13F.1, 14F.1, 15F.1
unnamed: 7E1.6, 13H41.19
unnamed: 7B2.1, 13J.76
unnamed: 7E1.3, 14H41.19
unnamed: 15A.2, 15C2.7
unnamed: 15A.1, 15C2.5
unnamed: 15A.3, 15C2.2
unnamed: 15C1.5, S240.7
unnamed: 7E1.11, 15C2.9
unnamed: 8G.6, 15H2.4
unnamed: 7E1.8, 16C.11
unnamed: 8B.2, R12.7
unnamed: 9B.2, R12.6
unnamed: 8B.10, R12.5
unnamed: 9B.4, R12.4
unnamed: 8B.12, R12.3
unnamed: 9B.6, R12.2
unnamed: 7B1.10, R13.7
unnamed: 9B.10, R13.6
unnamed: 8B.4, R13.5
unnamed: 9B.12, R13.4
unnamed: 8B.8, R13.3
unnamed: 8B.6, R13.2
unnamed: 7B1.12, R14.7
unnamed: 7B1.2, R14.6
unnamed: 9B.8, R14.5
unnamed: 7B1.4, R14.4
unnamed: 7B1.8, R14.3
unnamed: 7B1.6, R14.2
VCC: 1D.22, 1H.31, 1H.32, 2D.28, 2F.11, 2G1.14, 2G2.14, 2H.1, 2H.26, 2H.28, 2K.16, 2K.46, 2K.76, 2K.106, 3E.26, 3E.28, 3G.16, 3H.1, 3H.26, 3H.28, 3L.22, 3L.32, 4G.16, 4H.31, 4H.32, 5E.1, 5E.32, 5K.16, 5K.46, 5K.60, 5K.76, 5K.106, 5K.120, 6F.20, 6H.12, 6H.13, 6H.14, 6H.22, 6H.24, 6H.49, 7B.14, 7B1.14, 7B2.14, 7C.14, 7D1.1, 7D2.1, 7E1.14, 7E2.16, 7F2.16, 7G.1, 7G.4, 7G.13, 7G.14, 7H.1, 7H.4, 7H.10, 7H.14, 7J.14, 7K.1, 7K.20, 7K.28, 8B.14, 8D.24, 8G.14, 8J.4, 8J.14, 8K.1, 8K.20, 8K.28, 8L.22, 8L.32, 9B.14, 9D.24, 9G.16, 10D.16, 10G.14, 11D1.20, 11D2.24, 11E2.20, 11G1.14, 11G2.14, 11H1.1, 11H1.13, 11H1.14, 11H2.14, 12D.24, 12E.20, 12G.1, 12G.20, 12H.14, 12K.21, 12K.31, 12L.21, 12L.31, 13J.14, 13J.44, 13J.74, 13J.104, 14C.3, 14C.6, 14C.10, 14C.13, 14D.33, 14D.73, 14G41.16, 15A.8, 15C1.13, 15C2.16, 15G1.20, 15G2.20, 15H1.16, 15H2.13, 15H2.14, 16D.1, 16D.31, 16D.32, 16H.1, 16H.13, 16H.14, 16J.14, 16J.44, 16J.74, 16J.104, 16K.26, 16K.28, 16L.26, 16L.28, 18D.1, 18D.31, 18D.32, 18F.1, 18F.32, B10.4, C12.14, C14.14, F13.14, F19.14, H19.1, H19.2, H19.3, H19.28, H19.29, H19.39, H19.42, H19.43, H19.44, H19.45, H19.46, H19.53, H19.64, H19.78, H19.97, H19.98, H19.99, H19.100, H21.14, JP3.20, JP3.40, JP3.60, JP3.80, JP3.100, JP3.120, JP3.140, JP3.160, R12.1, R13.1, R14.1, U56.9
